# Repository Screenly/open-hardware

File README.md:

# open-hardware
Repository for Screenly's open hardware projects.

## Screenly CM5 Player

A digital signage player built on the Raspberry Pi Compute Module 5, with the CM4 as a fallback.

- **Display:** 2× HDMI Type A with CEC
- **Network:** Gigabit Ethernet; Wi-Fi and Bluetooth through an external antenna
- **USB:** 2× USB-A 3.0, 1× USB-C 2.0, and an internal USB-C for eMMC flashing
- **Storage:** CM5 eMMC, M.2 M-key NVMe, microSD slot (not fitted in the base variant)
- **Security:** TPM 2.0 (Infineon OPTIGA SLB 9672)
- **Audio:** stereo line output on a 3.5 mm jack (PCM5102A I2S DAC)
- **Power:** 9–16 V DC barrel jack
- **PCB:** 4 layers, 120 × 120 mm

| Item | Location |
| ---- | -------- |
| Specification | [screenly-cm5-player/docs/screenly-cm5-player-specifications.md](screenly-cm5-player/docs/screenly-cm5-player-specifications.md) |
| KiCad project | [screenly-cm5-player/electronics](screenly-cm5-player/electronics) |
| Bare PCB / assembly (`eMMC` variant) | `SRLY-PCB-000001` / `SRLY-ESP-000001` |

## Generating Manufacturing Files

`create-manufacturing-files.sh` creates every file needed to make a board from its KiCad project, with `kicad-cli`:

```
./create-manufacturing-files.sh --project=<project folder> --variant=<variant> \
    [--distributors=<distributor>,<distributor>,...] [--strict] [--db=<part database>]
```

`--db` (or the `PARTSDB_DIR` environment variable) is needed only in this early stage, while the part database is a local folder.[^partsdb]

For example: `./create-manufacturing-files.sh --project=screenly-cm5-player/electronics --variant=eMMC --distributors=LCSC,DigiKey`.

| Option | Meaning |
| ------ | ------- |
| `--project` | KiCad project folder (required) |
| `--variant` | Assembly variant (required) |
| `--distributors` | Optional distributor preference list. For each part, the script picks an approved part that meets the symbol's class key fields, preferring parts sold by distributors earlier in the list, then the design's own part (see [Distributor part numbers](docs/bom-standard.md#distributor-part-numbers)). A part sold by none of them gets its own preferred distributor, reported as a fallback. Without it, the design's parts are kept, each with its own preferred distributor. Names come from the distributor table of the part database (`tools/partsdb.py distributors list`), not case-sensitive. |
| `--strict` | Stop the run instead of falling back, or when a part has no distributor |
| `--db` | Part database folder; without it, `PARTSDB_DIR` is used |
| `--help` | Show the usage |

Options also accept a space instead of `=`, e.g. `--variant eMMC`.

The script runs ERC and DRC first and stops on errors. It writes into `<project folder>/outputs`:

| Output | Content |
| ------ | ------- |
| `manufacturing/pcb/<PCB_PN>.zip` | Gerbers, drill files, Gerber job file and fabrication notes, ready to upload to a PCB fab |
| `manufacturing/assembly/<ESP_PN>.zip` | BOM, HBOM (CycloneDX), pick-and-place files (CSV and KiCad `.pos`), assembly drawing (PDF) and assembly notes. The BOM is `<ESP_PN>-bom.csv`; with `--distributors`, the list is added in lowercase, e.g. `<ESP_PN>-bom-lcsc-digikey.csv` |
| `3d/<project>-<revision>.step.zip` | STEP model of the board |

Requirements:

- **Tools:** KiCad 10 (`kicad-cli`), Python 3 and `zip`. On the first run, the script installs `cyclonedx-python-lib` into a git-ignored `.venv/` for the HBOM.
- **Part database:** access through `tools/partsdb.py`, which reads part attributes for the HBOM. The database is private; see [How to Add Parts into the Library](docs/how-to-add-parts-into-the-library.md).
- **Project text variables** (KiCad: File → Project Setup → Text Variables):
  - `PCB_PN`: part number of the bare PCB;
  - `ESP_PN_<variant>`: part number of the assembly of each variant;
  - optional `FAB_*` and `ASM_*` variables for fabrication and assembly facts KiCad can't store, such as material, quality class and inspection. See `tools/manufacturing.py` for the list.
- **Board title block:** the revision, used in file names and notes.

Everything is generated from the source files, so fix the design or project settings rather than editing the outputs.

The ERC and DRC step is also a script of its own, `./check-erc-drc.sh --project=<project folder>`. On pull requests, CI runs it in KiCad 10 for every KiCad project the pull request adds.

The Python tools in `tools/` are formatted and linted with [ruff](https://docs.astral.sh/ruff/), configured in `ruff.toml`: run `ruff format tools` and `ruff check tools` before committing.

[^partsdb]: The part database will become a remote web service. Only `tools/partsdb.py` will change then, and `--db` and `PARTSDB_DIR` will be replaced by the service's own settings; the script itself stays the same.

## License

Copyright Screenly, Inc.

This source describes Open Hardware and is licensed under the CERN-OHL-P v2 (SPDX: `CERN-OHL-P-2.0`). See [LICENSE](LICENSE) for the full text.

You may redistribute and modify this source and make products using it under the terms of the CERN-OHL-P v2 (https://cern.ch/cern-ohl).

This source is distributed WITHOUT ANY EXPRESS OR IMPLIED WARRANTY, INCLUDING OF MERCHANTABILITY, SATISFACTORY QUALITY AND FITNESS FOR A PARTICULAR PURPOSE. Please see the CERN-OHL-P v2 for applicable conditions.

Source location: https://github.com/Screenly/open-hardware

Third-party 3D models in `library/3d-models` come from component manufacturers and the KiCad libraries, and remain under their owners' terms.

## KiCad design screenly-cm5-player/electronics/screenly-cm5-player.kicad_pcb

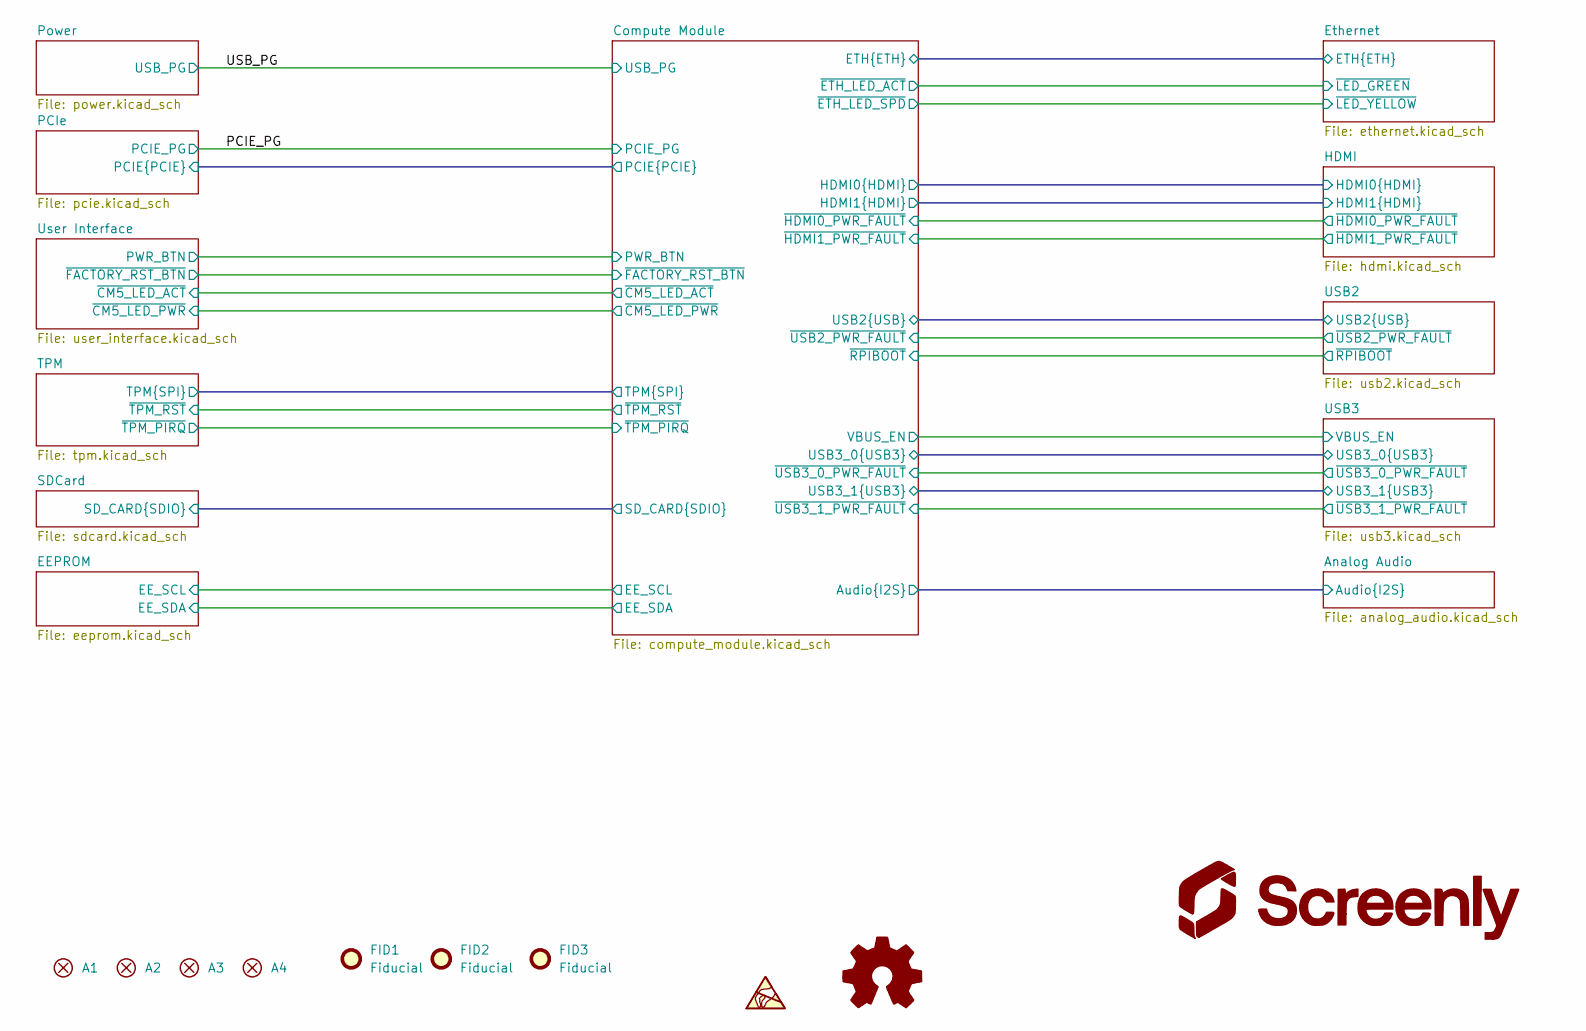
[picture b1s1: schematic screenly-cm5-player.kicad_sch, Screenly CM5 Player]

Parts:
A1, A2, A3, A4: AssemblyPoint; Screw_Hole_M2.2
FID1, FID2, FID3: Fiducial; Fiducial_1mm_Mask3mm
G1: ESD_Warning; ESD-Logo_8.9x8mm_SilkScreen
OSHW1: Logo_Open_Hardware_Small; OSHW-Logo_11.4x12mm_SilkScreen
ScreenlyLogo1: ScreenlyLogo; ScreenlyLogoFull_10mm

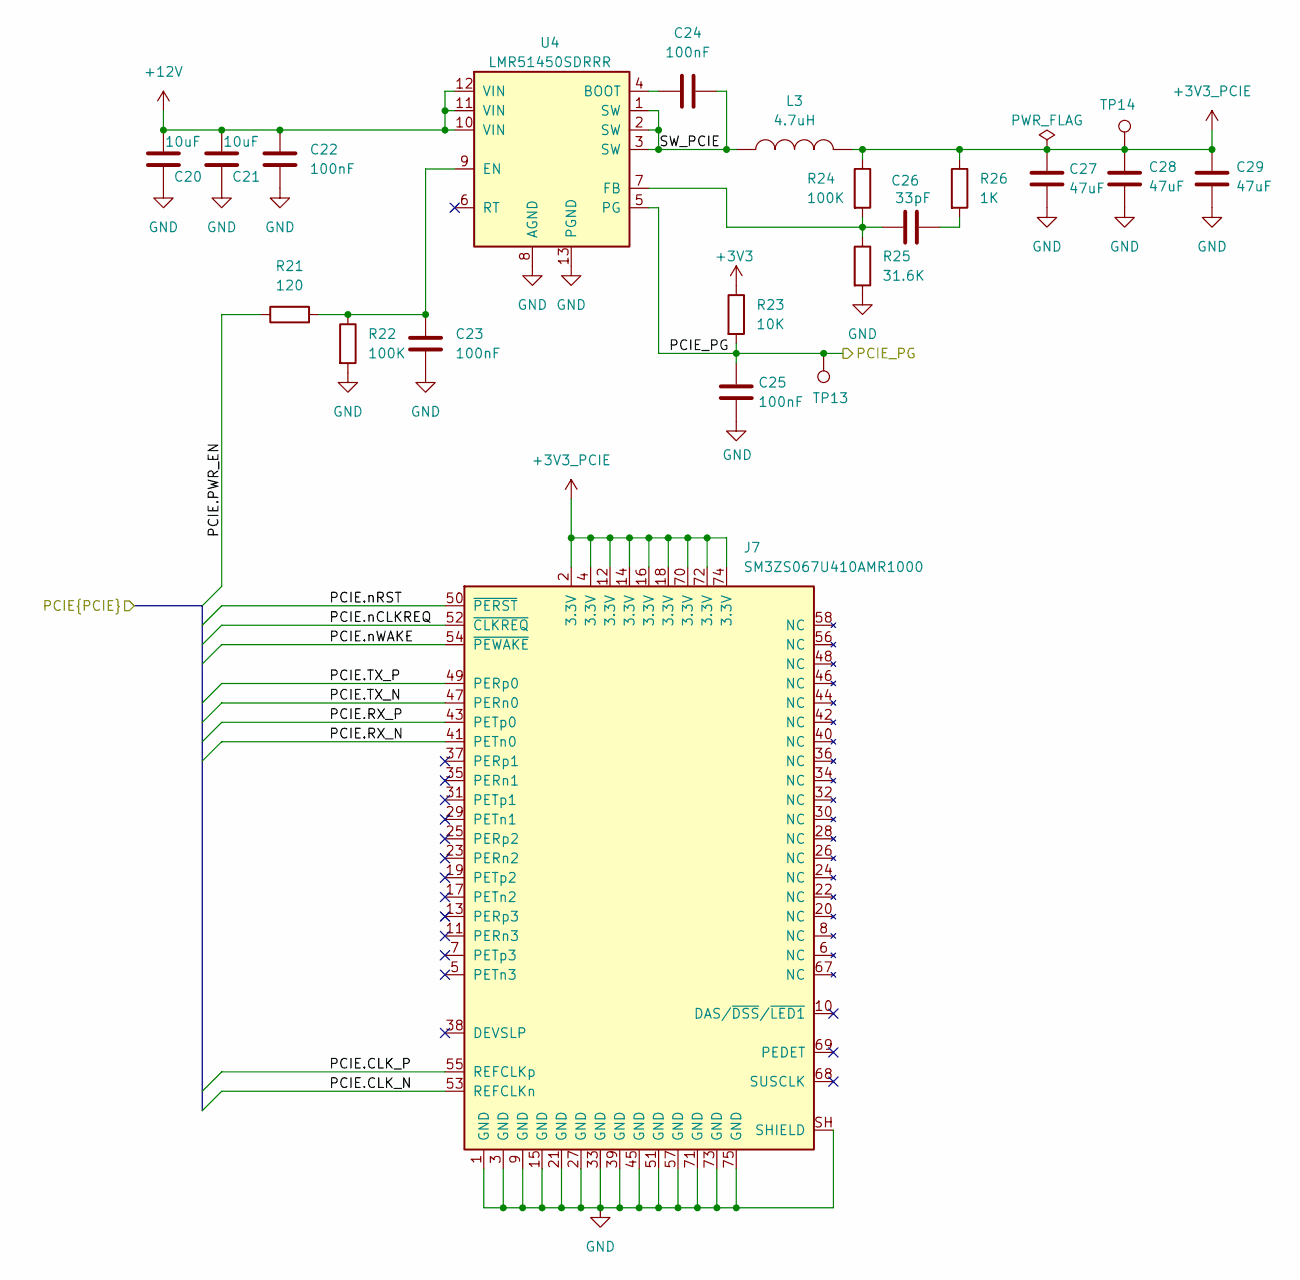
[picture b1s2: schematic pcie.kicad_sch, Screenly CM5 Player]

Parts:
C20, C21: 10uF; C_1210; tolerance 10%; voltage 50V; PartNumber SRLY-CAP-000002
C22, C23, C24, C25: 100nF; C_0402; tolerance 10%; voltage 50V; PartNumber SRLY-CAP-000001
C26: 33pF; C_0402; tolerance 5%; voltage 50V; PartNumber SRLY-CAP-000003
C27, C28, C29: 47uF; C_1210; tolerance 10%; voltage 10V; PartNumber SRLY-CAP-000005
J7: SM3ZS067U410AMR1000; M2_M-Key_JAE_SM3ZS067U410AMR1000_2230_2242_2280; PartNumber SRLY-CON-000006
L3: 4.7uH; L_Coilank_AAPS1050; tolerance 20%; PartNumber SRLY-IND-000001
R21: 120; R_0402; tolerance 10%; voltage 50V; PartNumber SRLY-RES-000009
R22, R24: 100K; R_0402; tolerance 1%; voltage 50V; PartNumber SRLY-RES-000004
R23: 10K; R_0402; tolerance 1%; voltage 50V; PartNumber SRLY-RES-000005
R25: 31.6K; R_0402; tolerance 1%; voltage 50V; PartNumber SRLY-RES-000010
R26: 1K; R_0402; tolerance 5%; voltage 50V; PartNumber SRLY-RES-000006
TP13, TP14: TestPoint; TestPoint_Pad_D2.0mm
U4: LMR51450SDRRR; TI_WSON-12-1EP_3x3mm_P0.5mm_EP1.3x2.5mm; PartNumber SRLY-PWR-000001

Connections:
+3V3: R23.1; also elsewhere on the board
+3V3_PCIE: C27.1, C28.1, C29.1, J7.2 (3.3V), J7.4 (3.3V), J7.12 (3.3V), J7.14 (3.3V), J7.16 (3.3V), J7.18 (3.3V), J7.70 (3.3V), J7.72 (3.3V), J7.74 (3.3V), L3.2, R24.1, R26.1, TP14.1 (1_1)
+12V: C20.1, C21.1, C22.1, U4.10 (VIN), U4.11 (VIN), U4.12 (VIN); also elsewhere on the board
/Compute Module/PCIE.CLK_N: J7.53 (REFCLKn); also elsewhere on the board
/Compute Module/PCIE.CLK_P: J7.55 (REFCLKp); also elsewhere on the board
/Compute Module/PCIE.PWR_EN: R21.1; also elsewhere on the board
/Compute Module/PCIE.RX_N: J7.41 (PETn0); also elsewhere on the board
/Compute Module/PCIE.RX_P: J7.43 (PETp0); also elsewhere on the board
/Compute Module/PCIE.TX_N: J7.47 (PERn0); also elsewhere on the board
/Compute Module/PCIE.TX_P: J7.49 (PERp0); also elsewhere on the board
/Compute Module/PCIE.nCLKREQ: J7.52 (~CLKREQ); also elsewhere on the board
/Compute Module/PCIE.nRST: J7.50 (~PERST); also elsewhere on the board
/Compute Module/PCIE.nWAKE: J7.54 (~PEWAKE); also elsewhere on the board
/PCIE_PG: C25.2, R23.2, TP13.1 (1_1), U4.5 (PG); also elsewhere on the board
/PCIe/SW_PCIE: C24.2, L3.1, U4.1 (SW), U4.2 (SW), U4.3 (SW)
GND: C20.2, C21.2, C22.2, C23.1, C25.1, C27.2, C28.2, C29.2, J7.1 (GND), J7.3 (GND), J7.9 (GND), J7.15 (GND), J7.21 (GND), J7.27 (GND), J7.33 (GND), J7.39 (GND), J7.45 (GND), J7.51 (GND), J7.57 (GND), J7.71 (GND), J7.73 (GND), J7.75 (GND), J7.SH (SHIELD), R22.2, R25.2, U4.8 (AGND), U4.13 (PGND); also elsewhere on the board
unnamed: C26.2, R26.2
unnamed: C24.1, U4.4 (BOOT)
unnamed: C23.2, R21.2, R22.1, U4.9 (EN)
unnamed: C26.1, R24.2, R25.1, U4.7 (FB)

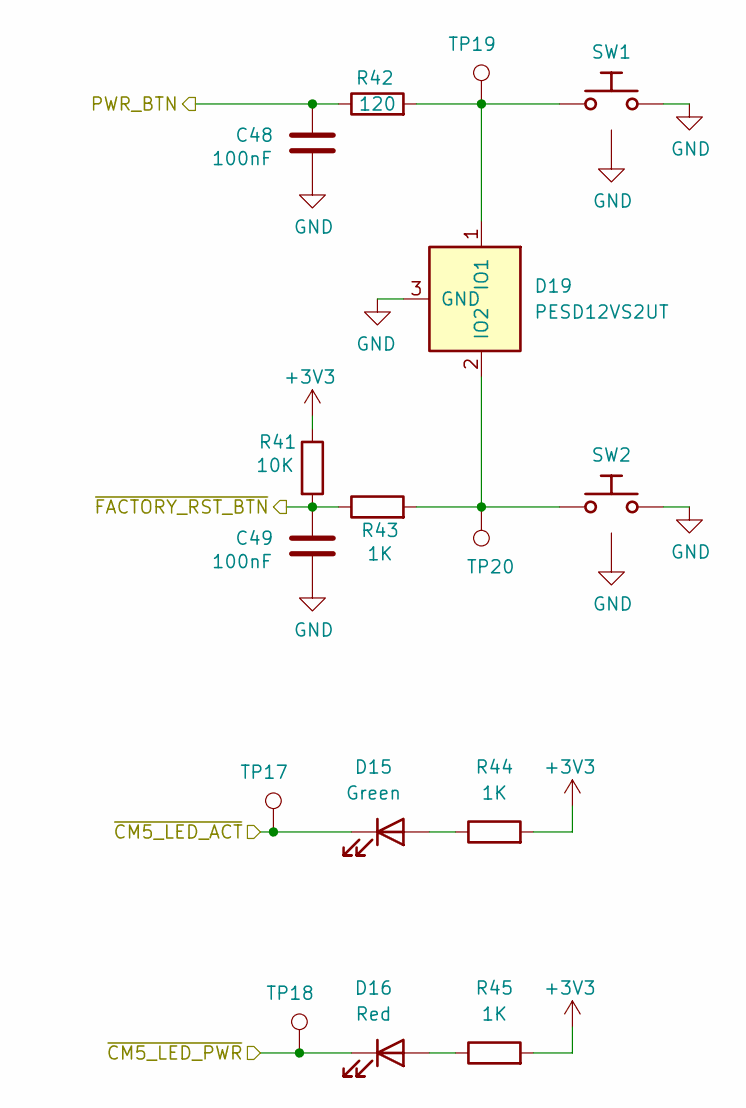
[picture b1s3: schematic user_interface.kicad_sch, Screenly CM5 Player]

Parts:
C48, C49: 100nF; C_0402; tolerance 10%; voltage 50V; PartNumber SRLY-CAP-000001
D15: Green; LED_LiteOn_LTST-S270_SideView; PartNumber SRLY-LED-000002
D16: Red; LED_LiteOn_LTST-S270_SideView; PartNumber SRLY-LED-000001
D19: PESD12VS2UT; SOT-23; PartNumber SRLY-DIO-000003
R41: 10K; R_0402; tolerance 1%; voltage 50V; PartNumber SRLY-RES-000005
R42: 120; R_0402; tolerance 10%; voltage 50V; PartNumber SRLY-RES-000009
R43, R44, R45: 1K; R_0402; tolerance 5%; voltage 50V; PartNumber SRLY-RES-000006
SW1, SW2: PTS645VM58-2; SW_Tactile_SPST_Angled_PTS645Vx58-2LFS; voltage 12V; PartNumber SRLY-SWC-000002
TP17, TP18, TP19, TP20: TestPoint; TestPoint_Pad_D2.0mm

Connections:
+3V3: R41.1, R44.2, R45.2; also elsewhere on the board
/Compute Module/PWR_BTN: C48.1, R42.1; also elsewhere on the board
/Compute Module/~CM5_LED_ACT: D15.1 (K), TP17.1 (1_1); also elsewhere on the board
/Compute Module/~CM5_LED_PWR: D16.1 (K), TP18.1 (1_1); also elsewhere on the board
/Compute Module/~FACTORY_RST_BTN: C49.1, R41.2, R43.1; also elsewhere on the board
GND: C48.2, C49.2, D19.3 (GND), SW1.2, SW1.SH, SW2.1, SW2.SH; also elsewhere on the board
unnamed: D15.2 (A), R44.1
unnamed: D16.2 (A), R45.1
unnamed: D19.1 (IO1), R42.2, SW1.1, TP19.1 (1_1)
unnamed: D19.2 (IO2), R43.2, SW2.2, TP20.1 (1_1)

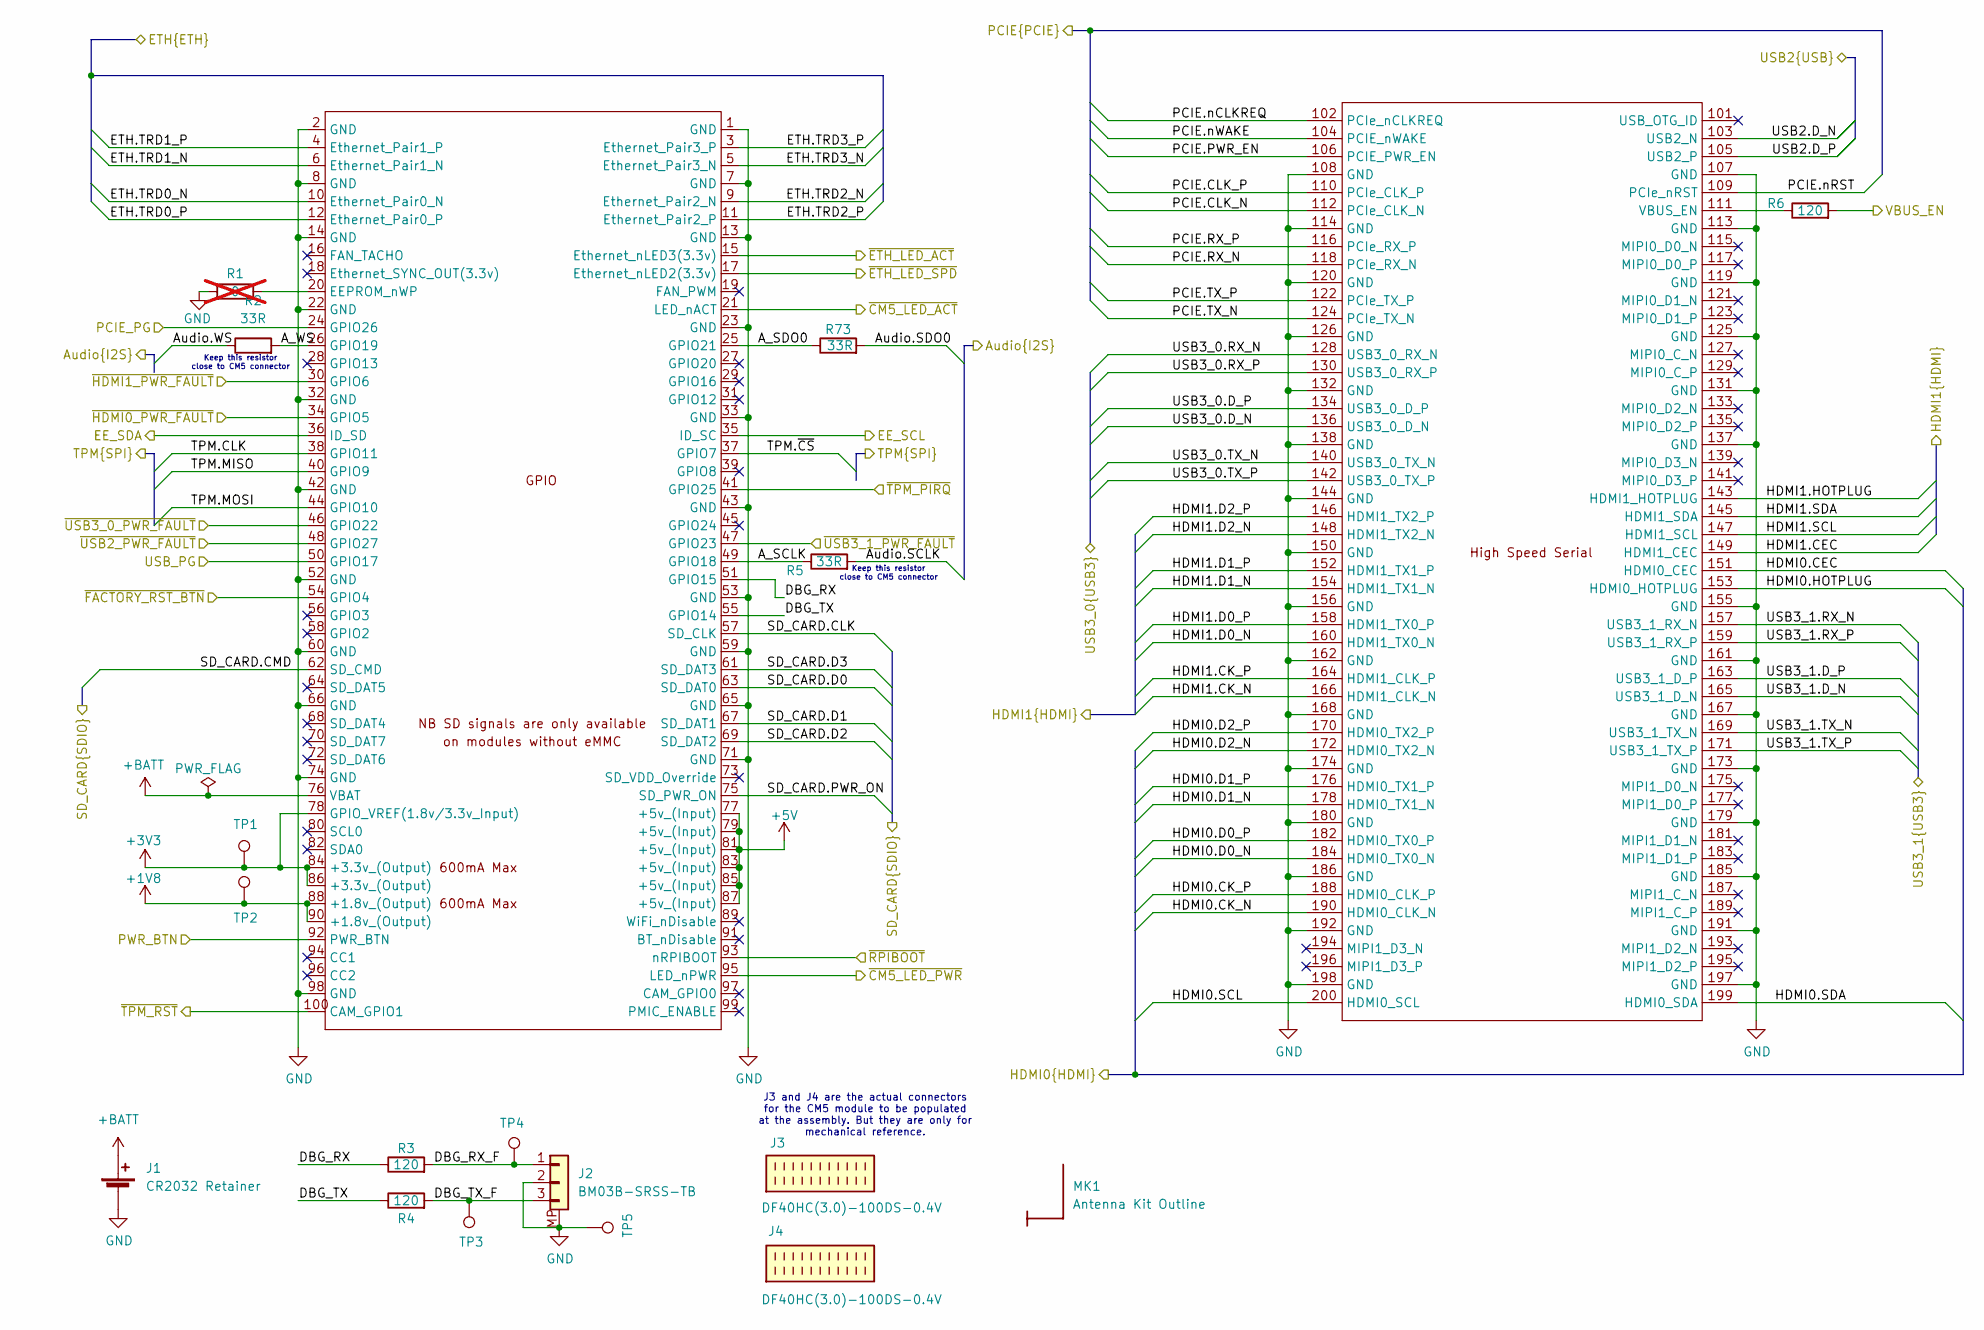
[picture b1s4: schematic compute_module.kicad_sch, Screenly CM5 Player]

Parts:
J1: CR2032 Retainer; BatteryHolder_MYOUNG_MY-2032-08_CR2032; PartNumber SRLY-CON-000014
J2: BM03B-SRSS-TB; JST_SH_BM03B-SRSS-TB_1x03-1MP_P1.00mm_Vertical; voltage 50V; PartNumber SRLY-CON-000015
J3, J4: DF40HC(3.0)-100DS-0.4V; Hirose_DF40HC-3.0-100DS-0.4V_2x50_P0.4mm_Vertical_NoCopper; PartNumber SRLY-CON-000016
MK1: Antenna Kit Outline; RaspberryPi_Antenna_Kit_Outline_SideView
R1: 0; SolderBridge_0402; tolerance 1%; voltage 50V; PartNumber SRLY-RES-000008; not fitted
R2, R5, R73: 33R; R_0402; tolerance 5%; voltage 50V; PartNumber SRLY-RES-000014
R3, R4, R6: 120; R_0402; tolerance 10%; voltage 50V; PartNumber SRLY-RES-000009
TP1, TP2, TP3, TP4, TP5: TestPoint; TestPoint_Pad_D2.0mm
U1: CM5104064; RaspberryPi-CM5; PartNumber SRLY-MOD-000001

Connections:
+1V8: TP2.1 (1_1), U1.88 (+1.8v_(Output)), U1.90 (+1.8v_(Output))
+3V3: TP1.1 (1_1), U1.78 (GPIO_VREF(1.8v/3.3v_Input)), U1.84 (+3.3v_(Output)), U1.86 (+3.3v_(Output)); also elsewhere on the board
+5V: U1.77 (+5v_(Input)), U1.79 (+5v_(Input)), U1.81 (+5v_(Input)), U1.83 (+5v_(Input)), U1.85 (+5v_(Input)), U1.87 (+5v_(Input)); also elsewhere on the board
+BATT: J1.1 (+), U1.76 (VBAT)
/Analog Audio/Audio.SCLK: R5.2; also elsewhere on the board
/Analog Audio/Audio.SDO0: R73.2; also elsewhere on the board
/Analog Audio/Audio.WS: R2.1; also elsewhere on the board
/Compute Module/A_SCLK: R5.1, U1.49 (GPIO18)
/Compute Module/A_SDO0: R73.1, U1.25 (GPIO21)
/Compute Module/A_WS: R2.2, U1.26 (GPIO19)
/Compute Module/DBG_RX: R3.1, U1.51 (GPIO15)
/Compute Module/DBG_RX_F: J2.1, R3.2, TP4.1 (1_1)
/Compute Module/DBG_TX: R4.1, U1.55 (GPIO14)
/Compute Module/DBG_TX_F: J2.3, R4.2, TP3.1 (1_1)
/Compute Module/EE_SCL: U1.35 (ID_SC); also elsewhere on the board
/Compute Module/EE_SDA: U1.36 (ID_SD); also elsewhere on the board
/Compute Module/ETH.TRD0_N: U1.10 (Ethernet_Pair0_N); also elsewhere on the board
/Compute Module/ETH.TRD0_P: U1.12 (Ethernet_Pair0_P); also elsewhere on the board
/Compute Module/ETH.TRD1_N: U1.6 (Ethernet_Pair1_N); also elsewhere on the board
/Compute Module/ETH.TRD1_P: U1.4 (Ethernet_Pair1_P); also elsewhere on the board
/Compute Module/ETH.TRD2_N: U1.9 (Ethernet_Pair2_N); also elsewhere on the board
/Compute Module/ETH.TRD2_P: U1.11 (Ethernet_Pair2_P); also elsewhere on the board
/Compute Module/ETH.TRD3_N: U1.5 (Ethernet_Pair3_N); also elsewhere on the board
/Compute Module/ETH.TRD3_P: U1.3 (Ethernet_Pair3_P); also elsewhere on the board
/Compute Module/HDMI0.CEC: U1.151 (HDMI0_CEC); also elsewhere on the board
/Compute Module/HDMI0.CK_N: U1.190 (HDMI0_CLK_N); also elsewhere on the board
/Compute Module/HDMI0.CK_P: U1.188 (HDMI0_CLK_P); also elsewhere on the board
/Compute Module/HDMI0.D0_N: U1.184 (HDMI0_TX0_N); also elsewhere on the board
/Compute Module/HDMI0.D0_P: U1.182 (HDMI0_TX0_P); also elsewhere on the board
/Compute Module/HDMI0.D1_N: U1.178 (HDMI0_TX1_N); also elsewhere on the board
/Compute Module/HDMI0.D1_P: U1.176 (HDMI0_TX1_P); also elsewhere on the board
/Compute Module/HDMI0.D2_N: U1.172 (HDMI0_TX2_N); also elsewhere on the board
/Compute Module/HDMI0.D2_P: U1.170 (HDMI0_TX2_P); also elsewhere on the board
/Compute Module/HDMI0.HOTPLUG: U1.153 (HDMI0_HOTPLUG); also elsewhere on the board
/Compute Module/HDMI0.SCL: U1.200 (HDMI0_SCL); also elsewhere on the board
/Compute Module/HDMI0.SDA: U1.199 (HDMI0_SDA); also elsewhere on the board
/Compute Module/HDMI1.CEC: U1.149 (HDMI1_CEC); also elsewhere on the board
/Compute Module/HDMI1.CK_N: U1.166 (HDMI1_CLK_N); also elsewhere on the board
/Compute Module/HDMI1.CK_P: U1.164 (HDMI1_CLK_P); also elsewhere on the board
/Compute Module/HDMI1.D0_N: U1.160 (HDMI1_TX0_N); also elsewhere on the board
/Compute Module/HDMI1.D0_P: U1.158 (HDMI1_TX0_P); also elsewhere on the board
/Compute Module/HDMI1.D1_N: U1.154 (HDMI1_TX1_N); also elsewhere on the board
/Compute Module/HDMI1.D1_P: U1.152 (HDMI1_TX1_P); also elsewhere on the board
/Compute Module/HDMI1.D2_N: U1.148 (HDMI1_TX2_N); also elsewhere on the board
/Compute Module/HDMI1.D2_P: U1.146 (HDMI1_TX2_P); also elsewhere on the board
/Compute Module/HDMI1.HOTPLUG: U1.143 (HDMI1_HOTPLUG); also elsewhere on the board
/Compute Module/HDMI1.SCL: U1.147 (HDMI1_SCL); also elsewhere on the board
/Compute Module/HDMI1.SDA: U1.145 (HDMI1_SDA); also elsewhere on the board
/Compute Module/PCIE.CLK_N: U1.112 (PCIe_CLK_N); also elsewhere on the board
/Compute Module/PCIE.CLK_P: U1.110 (PCIe_CLK_P); also elsewhere on the board
/Compute Module/PCIE.PWR_EN: U1.106 (PCIE_PWR_EN); also elsewhere on the board
/Compute Module/PCIE.RX_N: U1.118 (PCIe_RX_N); also elsewhere on the board
/Compute Module/PCIE.RX_P: U1.116 (PCIe_RX_P); also elsewhere on the board
/Compute Module/PCIE.TX_N: U1.124 (PCIe_TX_N); also elsewhere on the board
/Compute Module/PCIE.TX_P: U1.122 (PCIe_TX_P); also elsewhere on the board
/Compute Module/PCIE.nCLKREQ: U1.102 (PCIe_nCLKREQ); also elsewhere on the board
/Compute Module/PCIE.nRST: U1.109 (PCIe_nRST); also elsewhere on the board
/Compute Module/PCIE.nWAKE: U1.104 (PCIE_nWAKE); also elsewhere on the board
/Compute Module/PWR_BTN: U1.92 (PWR_BTN); also elsewhere on the board
/Compute Module/SD_CARD.CLK: U1.57 (SD_CLK); also elsewhere on the board
/Compute Module/SD_CARD.CMD: U1.62 (SD_CMD); also elsewhere on the board
/Compute Module/SD_CARD.D0: U1.63 (SD_DAT0); also elsewhere on the board
/Compute Module/SD_CARD.D1: U1.67 (SD_DAT1); also elsewhere on the board
/Compute Module/SD_CARD.D2: U1.69 (SD_DAT2); also elsewhere on the board
/Compute Module/SD_CARD.D3: U1.61 (SD_DAT3); also elsewhere on the board
/Compute Module/SD_CARD.PWR_ON: U1.75 (SD_PWR_ON); also elsewhere on the board
/Compute Module/TPM.CLK: U1.38 (GPIO11); also elsewhere on the board
/Compute Module/TPM.MISO: U1.40 (GPIO9); also elsewhere on the board
/Compute Module/TPM.MOSI: U1.44 (GPIO10); also elsewhere on the board
/Compute Module/TPM.~CS: U1.37 (GPIO7); also elsewhere on the board
/Compute Module/USB2.D_N: U1.103 (USB2_N); also elsewhere on the board
/Compute Module/USB2.D_P: U1.105 (USB2_P); also elsewhere on the board
/Compute Module/USB3_0.D_N: U1.136 (USB3_0_D_N); also elsewhere on the board
/Compute Module/USB3_0.D_P: U1.134 (USB3_0_D_P); also elsewhere on the board
/Compute Module/USB3_0.RX_N: U1.128 (USB3_0_RX_N); also elsewhere on the board
/Compute Module/USB3_0.RX_P: U1.130 (USB3_0_RX_P); also elsewhere on the board
/Compute Module/USB3_0.TX_N: U1.140 (USB3_0_TX_N); also elsewhere on the board
/Compute Module/USB3_0.TX_P: U1.142 (USB3_0_TX_P); also elsewhere on the board
/Compute Module/USB3_1.D_N: U1.165 (USB3_1_D_N); also elsewhere on the board
/Compute Module/USB3_1.D_P: U1.163 (USB3_1_D_P); also elsewhere on the board
/Compute Module/USB3_1.RX_N: U1.157 (USB3_1_RX_N); also elsewhere on the board
/Compute Module/USB3_1.RX_P: U1.159 (USB3_1_RX_P); also elsewhere on the board
/Compute Module/USB3_1.TX_N: U1.169 (USB3_1_TX_N); also elsewhere on the board
/Compute Module/USB3_1.TX_P: U1.171 (USB3_1_TX_P); also elsewhere on the board
/Compute Module/VBUS_EN: R6.2; also elsewhere on the board
/Compute Module/~CM5_LED_ACT: U1.21 (LED_nACT); also elsewhere on the board
/Compute Module/~CM5_LED_PWR: U1.95 (LED_nPWR); also elsewhere on the board
/Compute Module/~ETH_LED_ACT: U1.15 (Ethernet_nLED3(3.3v)); also elsewhere on the board
/Compute Module/~ETH_LED_SPD: U1.17 (Ethernet_nLED2(3.3v)); also elsewhere on the board
/Compute Module/~FACTORY_RST_BTN: U1.54 (GPIO4); also elsewhere on the board
/Compute Module/~HDMI0_PWR_FAULT: U1.34 (GPIO5); also elsewhere on the board
/Compute Module/~HDMI1_PWR_FAULT: U1.30 (GPIO6); also elsewhere on the board
/Compute Module/~RPIBOOT: U1.93 (nRPIBOOT); also elsewhere on the board
/Compute Module/~TPM_PIRQ: U1.41 (GPIO25); also elsewhere on the board
/Compute Module/~TPM_RST: U1.100 (CAM_GPIO1); also elsewhere on the board
/Compute Module/~USB2_PWR_FAULT: U1.48 (GPIO27); also elsewhere on the board
/Compute Module/~USB3_0_PWR_FAULT: U1.46 (GPIO22); also elsewhere on the board
/Compute Module/~USB3_1_PWR_FAULT: U1.47 (GPIO23); also elsewhere on the board
/PCIE_PG: U1.24 (GPIO26); also elsewhere on the board
/USB_PG: U1.50 (GPIO17); also elsewhere on the board
GND: J1.2 (-), J2.2, J2.MP, R1.1, TP5.1 (1_1), U1.1 (GND), U1.2 (GND), U1.7 (GND), U1.8 (GND), U1.13 (GND), U1.14 (GND), U1.22 (GND), U1.23 (GND), U1.32 (GND), U1.33 (GND), U1.42 (GND), U1.43 (GND), U1.52 (GND), U1.53 (GND), U1.59 (GND), U1.60 (GND), U1.65 (GND), U1.66 (GND), U1.71 (GND), U1.74 (GND), U1.98 (GND), U1.107 (GND), U1.108 (GND), U1.113 (GND), U1.114 (GND), U1.119 (GND), U1.120 (GND), U1.125 (GND), U1.126 (GND), U1.131 (GND), U1.132 (GND), U1.137 (GND), U1.138 (GND), U1.144 (GND), U1.150 (GND), U1.155 (GND), U1.156 (GND), U1.161 (GND), U1.162 (GND), U1.167 (GND), U1.168 (GND), U1.173 (GND), U1.174 (GND), U1.179 (GND), U1.180 (GND), U1.185 (GND), U1.186 (GND), U1.191 (GND), U1.192 (GND), U1.197 (GND), U1.198 (GND); also elsewhere on the board
unnamed: R1.2, U1.20 (EEPROM_nWP)
unnamed: R6.1, U1.111 (VBUS_EN)

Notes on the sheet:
Keep this resistor close to CM5 connector
J3 and J4 are the actual connectors for the CM5 module to be populated at the assembly. But they are only for mechanical reference.

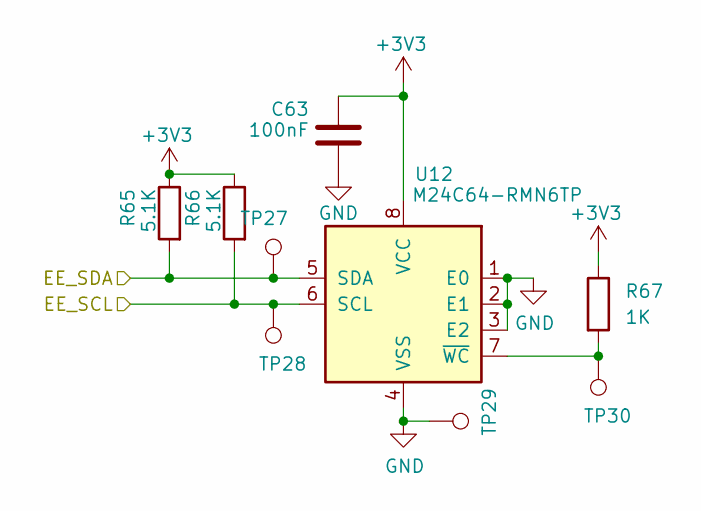
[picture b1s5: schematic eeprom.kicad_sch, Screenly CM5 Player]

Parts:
C63: 100nF; C_0402; tolerance 10%; voltage 50V; PartNumber SRLY-CAP-000001
R65, R66: 5.1K; R_0402; tolerance 1%; voltage 50V; PartNumber SRLY-RES-000012
R67: 1K; R_0402; tolerance 5%; voltage 50V; PartNumber SRLY-RES-000006
TP27, TP28, TP29, TP30: TestPoint; TestPoint_Pad_D2.0mm
U12: M24C64-RMN6TP; SOIC-8_3.9x4.9mm_P1.27mm; PartNumber SRLY-STO-000001

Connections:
+3V3: C63.1, R65.1, R66.1, R67.1, U12.8 (VCC); also elsewhere on the board
/Compute Module/EE_SCL: R66.2, TP28.1 (1_1), U12.6 (SCL); also elsewhere on the board
/Compute Module/EE_SDA: R65.2, TP27.1 (1_1), U12.5 (SDA); also elsewhere on the board
GND: C63.2, TP29.1 (1_1), U12.1 (E0), U12.2 (E1), U12.3 (E2), U12.4 (VSS); also elsewhere on the board
unnamed: R67.2, TP30.1 (1_1), U12.7 (~WC)

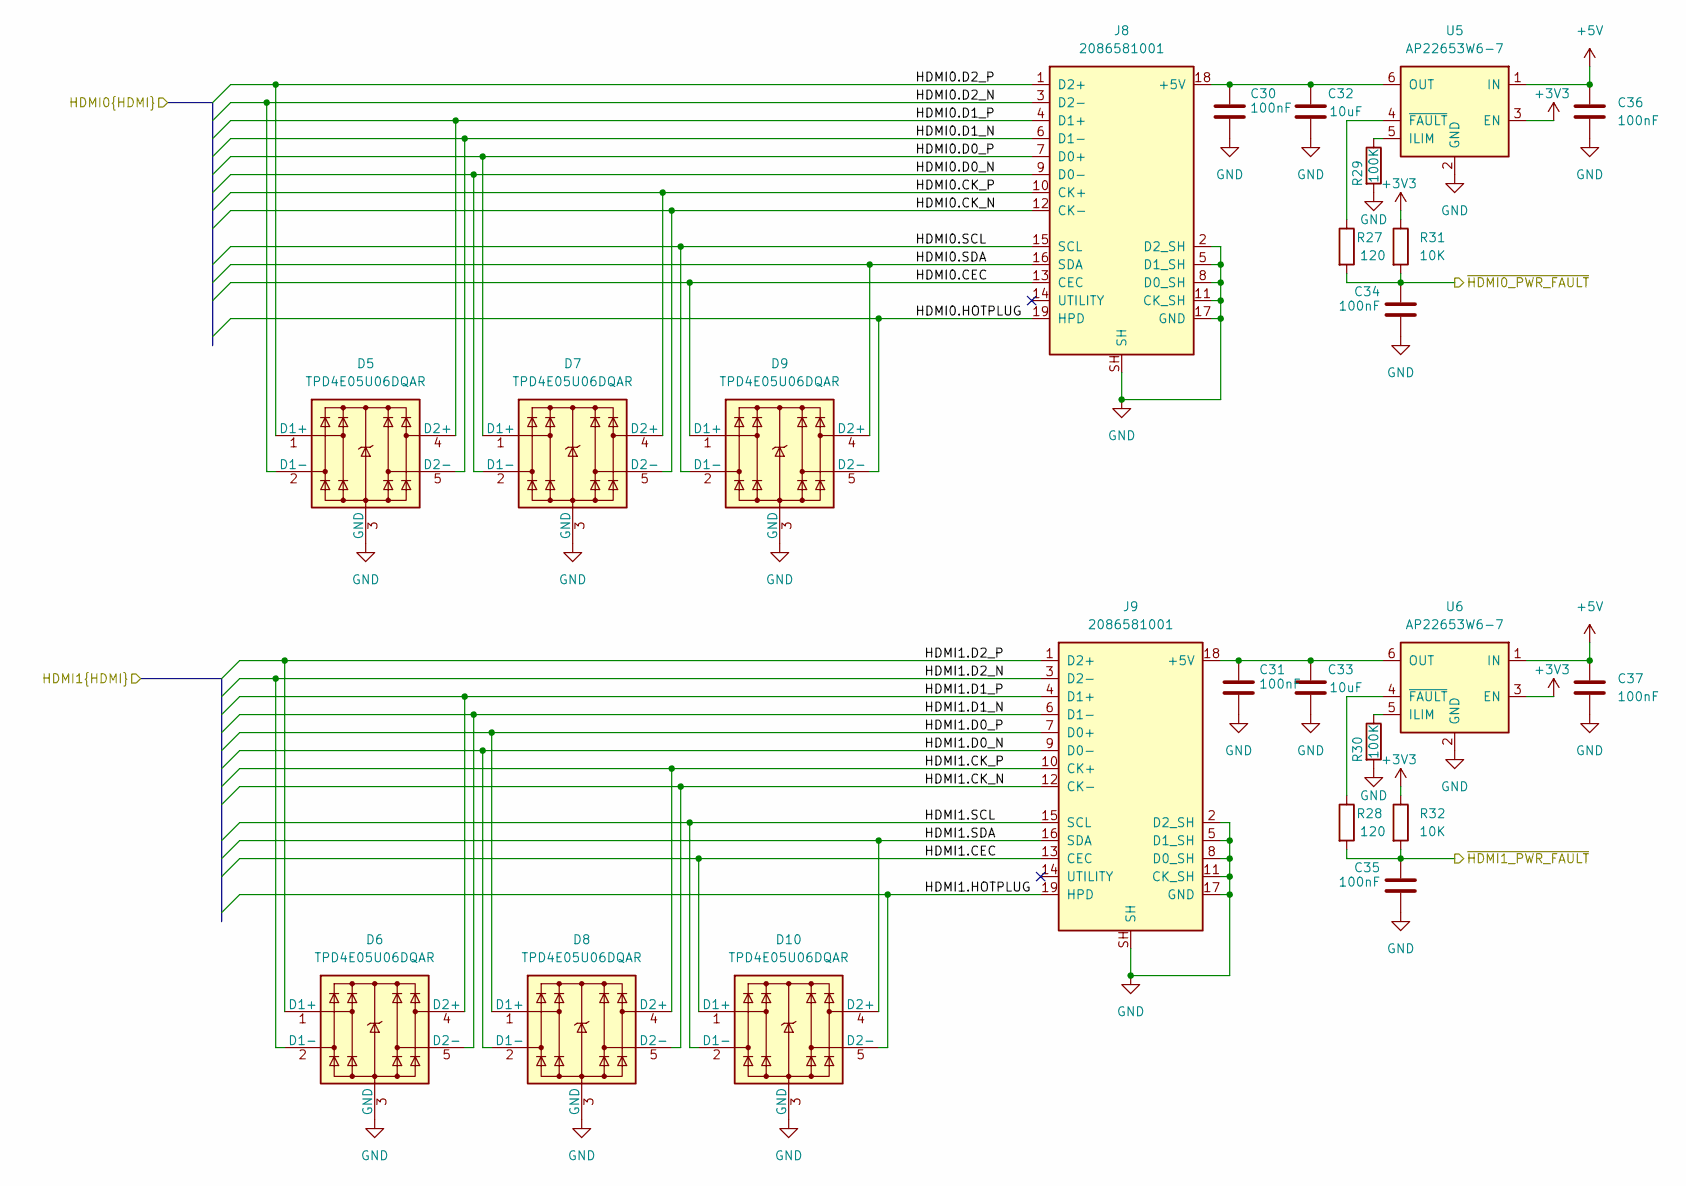
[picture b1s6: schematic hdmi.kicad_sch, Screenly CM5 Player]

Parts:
C30, C31, C34, C35, C36, C37: 100nF; C_0402; tolerance 10%; voltage 50V; PartNumber SRLY-CAP-000001
C32, C33: 10uF; C_1210; tolerance 10%; voltage 50V; PartNumber SRLY-CAP-000002
D5, D6, D7, D8, D9, D10: TPD4E05U06DQAR; TI_USON-10_2.5x1.0mm_P0.5mm; PartNumber SRLY-DIO-000004
J8, J9: 2086581001; HDMI_A_Molex_208658-1001_Horizontal; voltage 40V; PartNumber SRLY-CON-000007
R27, R28: 120; R_0402; tolerance 5%; voltage 50V; PartNumber SRLY-RES-000009
R29, R30: 100K; R_0402; tolerance 1%; voltage 50V; PartNumber SRLY-RES-000004
R31, R32: 10K; R_0402; tolerance 1%; voltage 50V; PartNumber SRLY-RES-000005
U5, U6: AP22653W6-7; SOT-23-6; PartNumber SRLY-PWR-000003

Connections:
+3V3: R31.1, R32.1, U5.3 (EN), U6.3 (EN); also elsewhere on the board
+5V: C36.1, C37.1, U5.1 (IN), U6.1 (IN); also elsewhere on the board
/Compute Module/HDMI0.CEC: D9.1 (D1+), D9.10, J8.13 (CEC); also elsewhere on the board
/Compute Module/HDMI0.CK_N: D7.5 (D2-), D7.6, J8.12 (CK-); also elsewhere on the board
/Compute Module/HDMI0.CK_P: D7.4 (D2+), D7.7, J8.10 (CK+); also elsewhere on the board
/Compute Module/HDMI0.D0_N: D7.2 (D1-), D7.9, J8.9 (D0-); also elsewhere on the board
/Compute Module/HDMI0.D0_P: D7.1 (D1+), D7.10, J8.7 (D0+); also elsewhere on the board
/Compute Module/HDMI0.D1_N: D5.5 (D2-), D5.6, J8.6 (D1-); also elsewhere on the board
/Compute Module/HDMI0.D1_P: D5.4 (D2+), D5.7, J8.4 (D1+); also elsewhere on the board
/Compute Module/HDMI0.D2_N: D5.2 (D1-), D5.9, J8.3 (D2-); also elsewhere on the board
/Compute Module/HDMI0.D2_P: D5.1 (D1+), D5.10, J8.1 (D2+); also elsewhere on the board
/Compute Module/HDMI0.HOTPLUG: D9.5 (D2-), D9.6, J8.19 (HPD); also elsewhere on the board
/Compute Module/HDMI0.SCL: D9.2 (D1-), D9.9, J8.15 (SCL); also elsewhere on the board
/Compute Module/HDMI0.SDA: D9.4 (D2+), D9.7, J8.16 (SDA); also elsewhere on the board
/Compute Module/HDMI1.CEC: D10.1 (D1+), D10.10, J9.13 (CEC); also elsewhere on the board
/Compute Module/HDMI1.CK_N: D8.5 (D2-), D8.6, J9.12 (CK-); also elsewhere on the board
/Compute Module/HDMI1.CK_P: D8.4 (D2+), D8.7, J9.10 (CK+); also elsewhere on the board
/Compute Module/HDMI1.D0_N: D8.2 (D1-), D8.9, J9.9 (D0-); also elsewhere on the board
/Compute Module/HDMI1.D0_P: D8.1 (D1+), D8.10, J9.7 (D0+); also elsewhere on the board
/Compute Module/HDMI1.D1_N: D6.5 (D2-), D6.6, J9.6 (D1-); also elsewhere on the board
/Compute Module/HDMI1.D1_P: D6.4 (D2+), D6.7, J9.4 (D1+); also elsewhere on the board
/Compute Module/HDMI1.D2_N: D6.2 (D1-), D6.9, J9.3 (D2-); also elsewhere on the board
/Compute Module/HDMI1.D2_P: D6.1 (D1+), D6.10, J9.1 (D2+); also elsewhere on the board
/Compute Module/HDMI1.HOTPLUG: D10.5 (D2-), D10.6, J9.19 (HPD); also elsewhere on the board
/Compute Module/HDMI1.SCL: D10.2 (D1-), D10.9, J9.15 (SCL); also elsewhere on the board
/Compute Module/HDMI1.SDA: D10.4 (D2+), D10.7, J9.16 (SDA); also elsewhere on the board
/Compute Module/~HDMI0_PWR_FAULT: C34.1, R27.2, R31.2; also elsewhere on the board
/Compute Module/~HDMI1_PWR_FAULT: C35.1, R28.2, R32.2; also elsewhere on the board
GND: C30.2, C31.2, C32.2, C33.2, C34.2, C35.2, C36.2, C37.2, D5.3 (GND), D5.8 (GND), D6.3 (GND), D6.8 (GND), D7.3 (GND), D7.8 (GND), D8.3 (GND), D8.8 (GND), D9.3 (GND), D9.8 (GND), D10.3 (GND), D10.8 (GND), J8.2 (D2_SH), J8.5 (D1_SH), J8.8 (D0_SH), J8.11 (CK_SH), J8.17 (GND), J8.SH, J9.2 (D2_SH), J9.5 (D1_SH), J9.8 (D0_SH), J9.11 (CK_SH), J9.17 (GND), J9.SH, R29.2, R30.2, U5.2 (GND), U6.2 (GND); also elsewhere on the board
unnamed: C30.1, C32.1, J8.18 (+5V), U5.6 (OUT)
unnamed: C31.1, C33.1, J9.18 (+5V), U6.6 (OUT)
unnamed: R29.1, U5.5 (ILIM)
unnamed: R27.1, U5.4 (~FAULT)
unnamed: R30.1, U6.5 (ILIM)
unnamed: R28.1, U6.4 (~FAULT)
